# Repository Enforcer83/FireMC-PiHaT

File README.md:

# FireMC-3.14

FireMC for the Raspberry Pi HaT system

## 

This project has moved to https://gitlab.com/Enforcer83/FireMC-PiHaT.  See you there.

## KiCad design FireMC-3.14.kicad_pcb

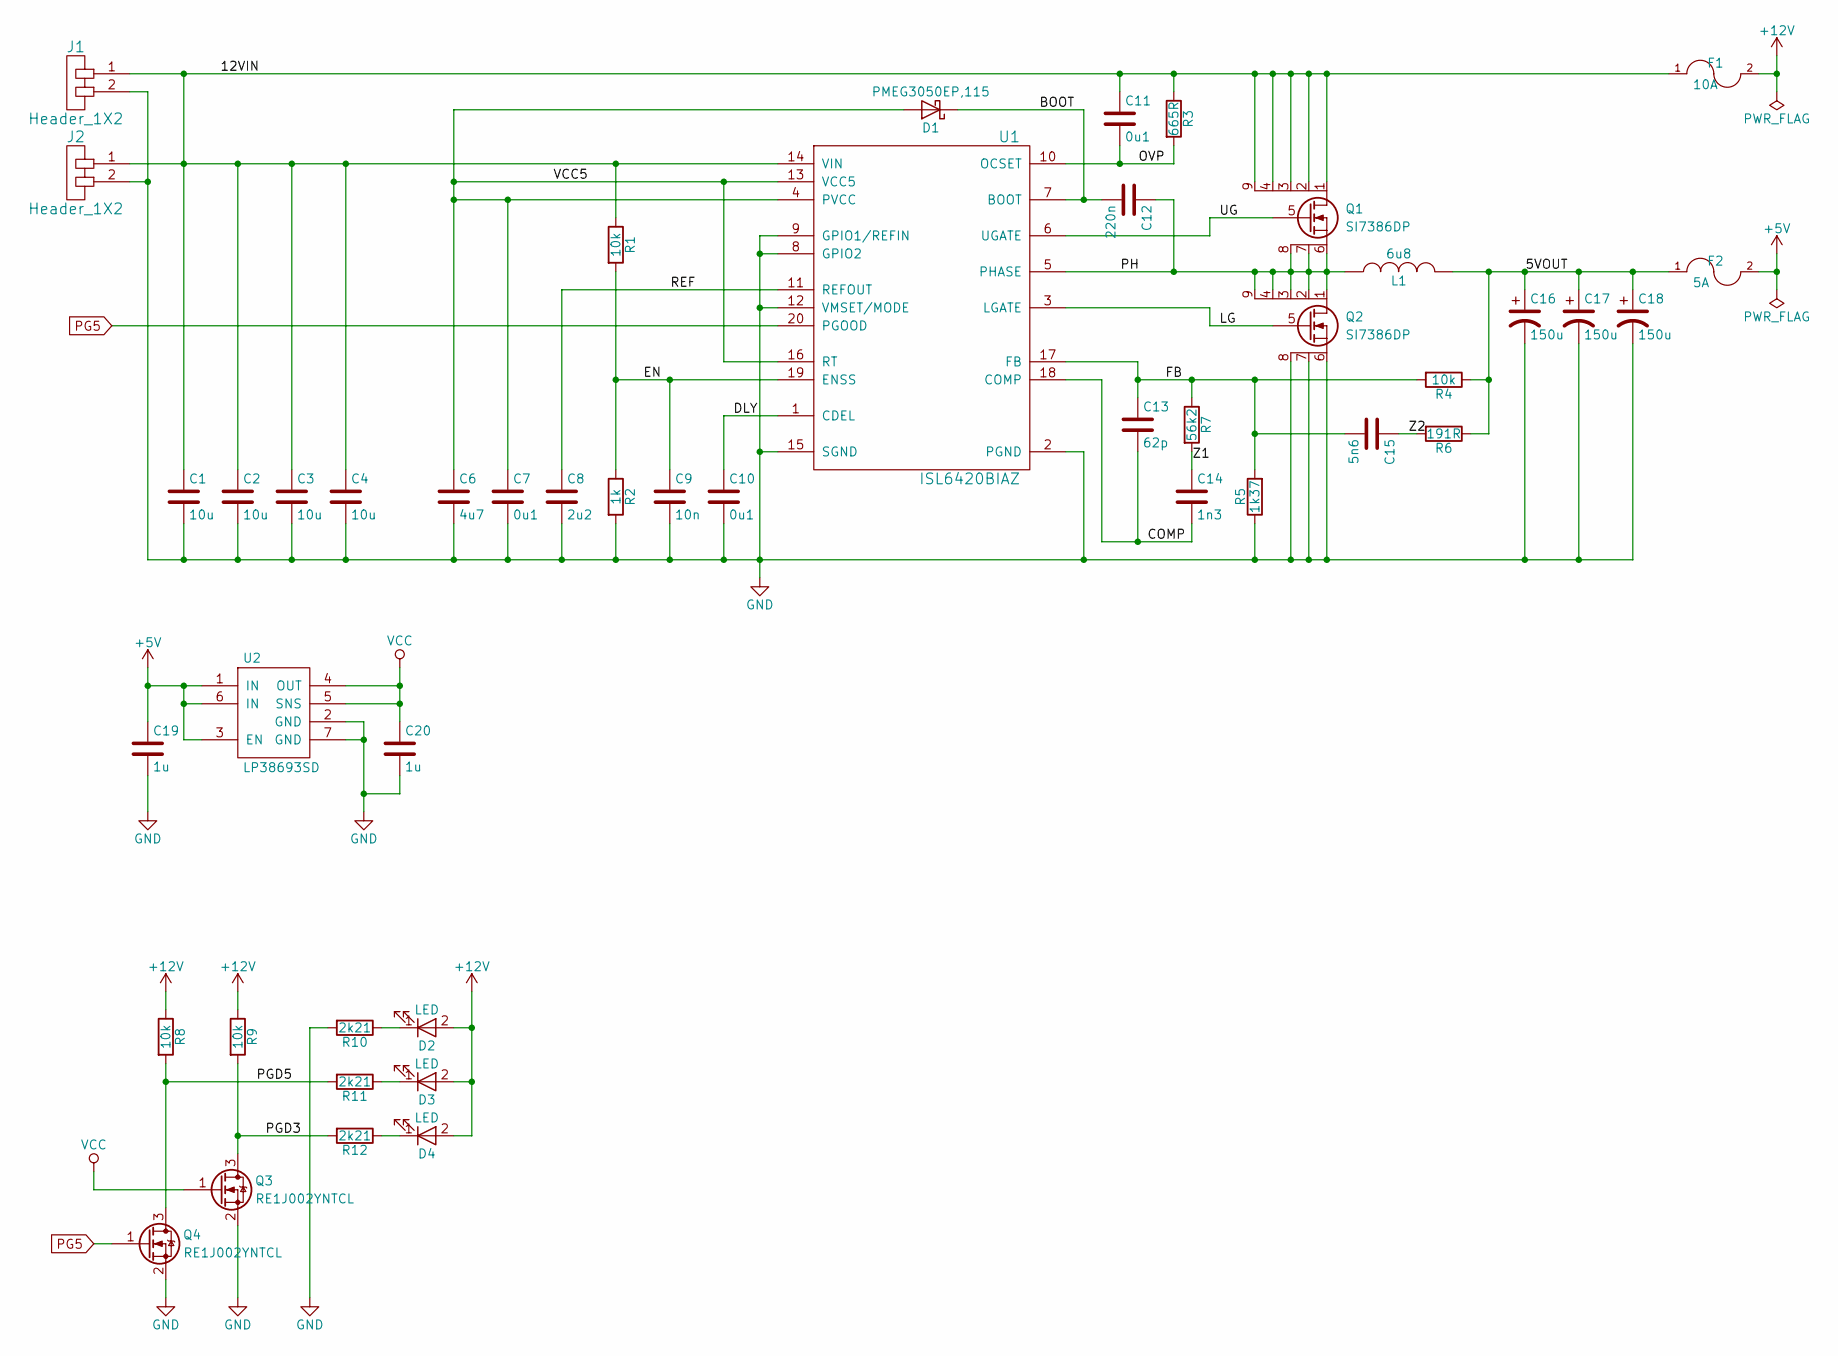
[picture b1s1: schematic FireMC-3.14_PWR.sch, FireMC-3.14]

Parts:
C1, C2, C3, C4: 10u; CAPC1608X95N
C6: 4u7; CAPC1608X95N
C7, C10, C11: 0u1; CAPC1608X90N
C8: 2u2; CAPC1608X90N
C9: 10n; CAPC1608X90N
C12: 220n; CAPC1608X90N
C13: 62p; CAPC1608X90N
C14: 1n3; CAPC1608X90N
C15: 5n6; CAPC1608X90N
C16, C17, C18: 150u; CAPAE660X770N
C19, C20: 1u; CAPC1608X90N
D1: PMEG3050EP,115; SOD4725X100N
D2, D3, D4: LED; LEDM1608X70N
F1: 10A; MPD_BK-6010; Mfg PN 0ATO010.V
F2: 5A; MPD_BK-6010; Mfg PN 0ATO005.V
J1: Header_1X2; MOLEX_395321002; MFG P/N 0395321002
J2: Header_1X2; PHEONIX_1923869; MFG P/N 1923869
L1: 6u8; INDM1213X620N
Q1, Q2: SI7386DP; SON9P127_490X590X112L61X41T376X348N
Q3, Q4: RE1J002YNTCL; SOTFL3P50_160X85L45X28N
R1, R4, R8, R9: 10k; RESC1608X55N
R2: 1k; RESC1608X55N
R3: 665R; RESC1608X55N
R5: 1k37; RESC1608X55N
R6: 191R; RESC1608X55N
R7: 56k2; RESC1608X55N
R10, R11, R12: 2k21; RESC1608X55N
U1: ISL6420BIAZ; SOP63P600X155-20N
U2: LP38693SD; SON7P95_300X300X80L40X35T210X160N

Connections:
+5V: C19.1, F2.2, U2.1 (IN), U2.3 (EN), U2.6 (IN); also elsewhere on the board
+12V: D2.2 (A), D3.2 (A), D4.2 (A), F1.2, R8.1, R9.1; also elsewhere on the board
/Power/5VOUT: C16.1, C17.1, C18.1, F2.1, L1.2, R4.1, R6.1
/Power/12VIN: C1.1, C2.1, C3.1, C4.1, C11.1, F1.1, J1.1, J2.1, Q1.1 (D), Q1.2 (D), Q1.3 (D), Q1.4 (D), Q1.9 (D), R1.1, R3.1, U1.14 (VIN)
/Power/BOOT: C12.2, D1.1 (K), U1.7 (BOOT)
/Power/COMP: C13.2, C14.2, U1.18 (COMP)
/Power/DLY: C10.1, U1.1 (CDEL)
/Power/EN: C9.1, R1.2, R2.1, U1.19 (ENSS)
/Power/FB: C13.1, C15.2, R4.2, R5.2, R7.1, U1.17 (FB)
/Power/LG: Q2.5 (G), U1.3 (LGATE)
/Power/OVP: C11.2, R3.2, U1.10 (OCSET)
/Power/PGD3: Q3.3 (D), R9.2, R12.2
/Power/PGD5: Q4.3 (D), R8.2, R11.2
/Power/PH: C12.1, L1.1, Q1.6 (S), Q1.7 (S), Q1.8 (S), Q2.1 (D), Q2.2 (D), Q2.3 (D), Q2.4 (D), Q2.9 (D), U1.5 (PHASE)
/Power/REF: C8.1, U1.11 (REFOUT)
/Power/UG: Q1.5 (G), U1.6 (UGATE)
/Power/VCC5: C6.1, C7.1, D1.2 (A), U1.4 (PVCC), U1.13 (VCC5), U1.16 (RT)
/Power/Z1: C14.1, R7.2
/Power/Z2: C15.1, R6.2
GND: C1.2, C2.2, C3.2, C4.2, C6.2, C7.2, C8.2, C9.2, C10.2, C16.2, C17.2, C18.2, C19.2, C20.2, J1.2, J2.2, Q2.6 (S), Q2.7 (S), Q2.8 (S), Q3.2 (S), Q4.2 (S), R2.2, R5.1, R10.2, U1.2 (PGND), U1.8 (GPIO2), U1.9 (GPIO1/REFIN), U1.12 (VMSET/MODE), U1.15 (SGND), U2.2 (GND), U2.7 (GND); also elsewhere on the board
unnamed: D2.1 (K), R10.1
unnamed: D3.1 (K), R11.1
unnamed: D4.1 (K), R12.1
PG5: Q4.1 (G), U1.20 (PGOOD)
VCC: C20.1, Q3.1 (G), U2.4 (OUT), U2.5 (SNS); also elsewhere on the board

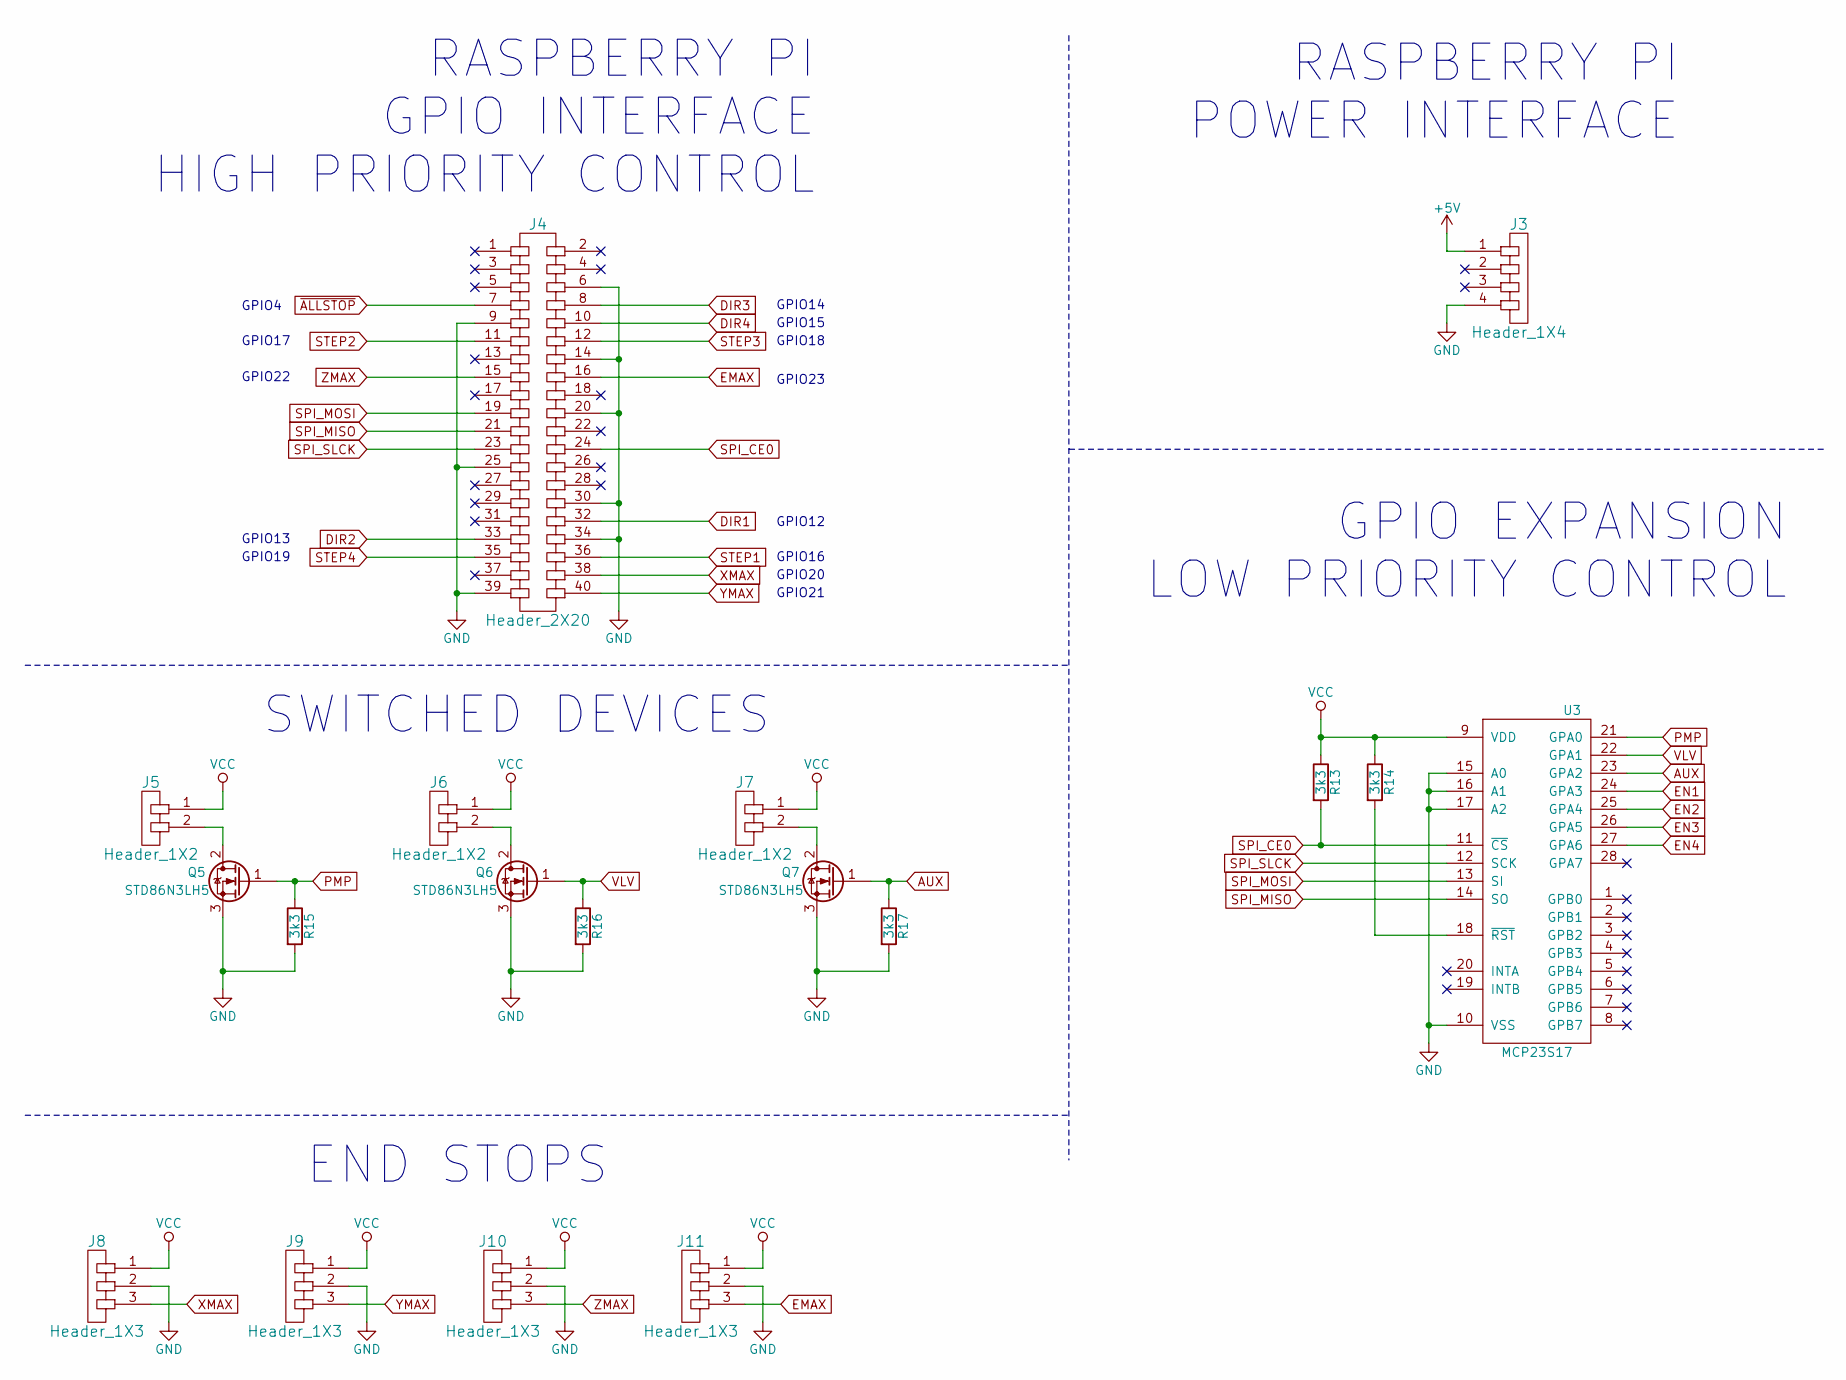
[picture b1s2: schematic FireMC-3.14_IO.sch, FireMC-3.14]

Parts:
J3: Header_1X4; MOLEX_22-23-2041
J4: Header_2X20; SULLINS_PPTC202LFBN-RC; Mfg PN PPPC200LFBN-RC
J5, J6, J7: Header_1X2; SULLINS_PRPC002SAAN-RC
J8, J9, J10, J11: Header_1X3; SULLINS_PRPC003SAAN-RC
Q5, Q6, Q7: STD86N3LH5; TO228P972X240-3N
R13, R14, R15, R16, R17: 3k3; RESC1608X55N
U3: MCP23S17; SOIC127P1030X265-28N

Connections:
+5V: J3.1; also elsewhere on the board
AUX: Q7.1 (G), R17.1, U3.23 (GPA2)
DIR1: J4.32; also elsewhere on the board
DIR2: J4.33; also elsewhere on the board
DIR3: J4.8; also elsewhere on the board
DIR4: J4.10; also elsewhere on the board
EMAX: J4.16, J11.3
EN1: U3.24 (GPA3); also elsewhere on the board
EN2: U3.25 (GPA4); also elsewhere on the board
EN3: U3.26 (GPA5); also elsewhere on the board
EN4: U3.27 (GPA6); also elsewhere on the board
GND: J3.4, J4.6, J4.9, J4.14, J4.20, J4.25, J4.30, J4.34, J4.39, J8.2, J9.2, J10.2, J11.2, Q5.3 (S), Q6.3 (S), Q7.3 (S), R15.2, R16.2, R17.2, U3.10 (VSS), U3.15 (A0), U3.16 (A1), U3.17 (A2); also elsewhere on the board
unnamed: J5.2, Q5.2 (D)
unnamed: J6.2, Q6.2 (D)
unnamed: J7.2, Q7.2 (D)
unnamed: R14.2, U3.18 (~RST)
PMP: Q5.1 (G), R15.1, U3.21 (GPA0)
SPI_CE0: J4.24, R13.2, U3.11 (~CS)
SPI_MISO: J4.21, U3.14 (SO)
SPI_MOSI: J4.19, U3.13 (SI)
SPI_SLCK: J4.23, U3.12 (SCK)
STEP1: J4.36; also elsewhere on the board
STEP2: J4.11; also elsewhere on the board
STEP3: J4.12; also elsewhere on the board
STEP4: J4.35; also elsewhere on the board
VCC: J5.1, J6.1, J7.1, J8.1, J9.1, J10.1, J11.1, R13.1, R14.1, U3.9 (VDD); also elsewhere on the board
VLV: Q6.1 (G), R16.1, U3.22 (GPA1)
XMAX: J4.38, J8.3
YMAX: J4.40, J9.3
ZMAX: J4.15, J10.3
~ALLSTOP: J4.7; also elsewhere on the board

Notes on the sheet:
RASPBERRY PI GPIO INTERFACE HIGH PRIORITY CONTROL
RASPBERRY PI POWER INTERFACE
GPIO EXPANSION LOW PRIORITY CONTROL
SWITCHED DEVICES
END STOPS
GPIO12
GPIO13
GPIO14
GPIO15
GPIO16
GPIO17
GPIO18
GPIO19
GPIO20
GPIO21
GPIO22
GPIO4
GPIO23

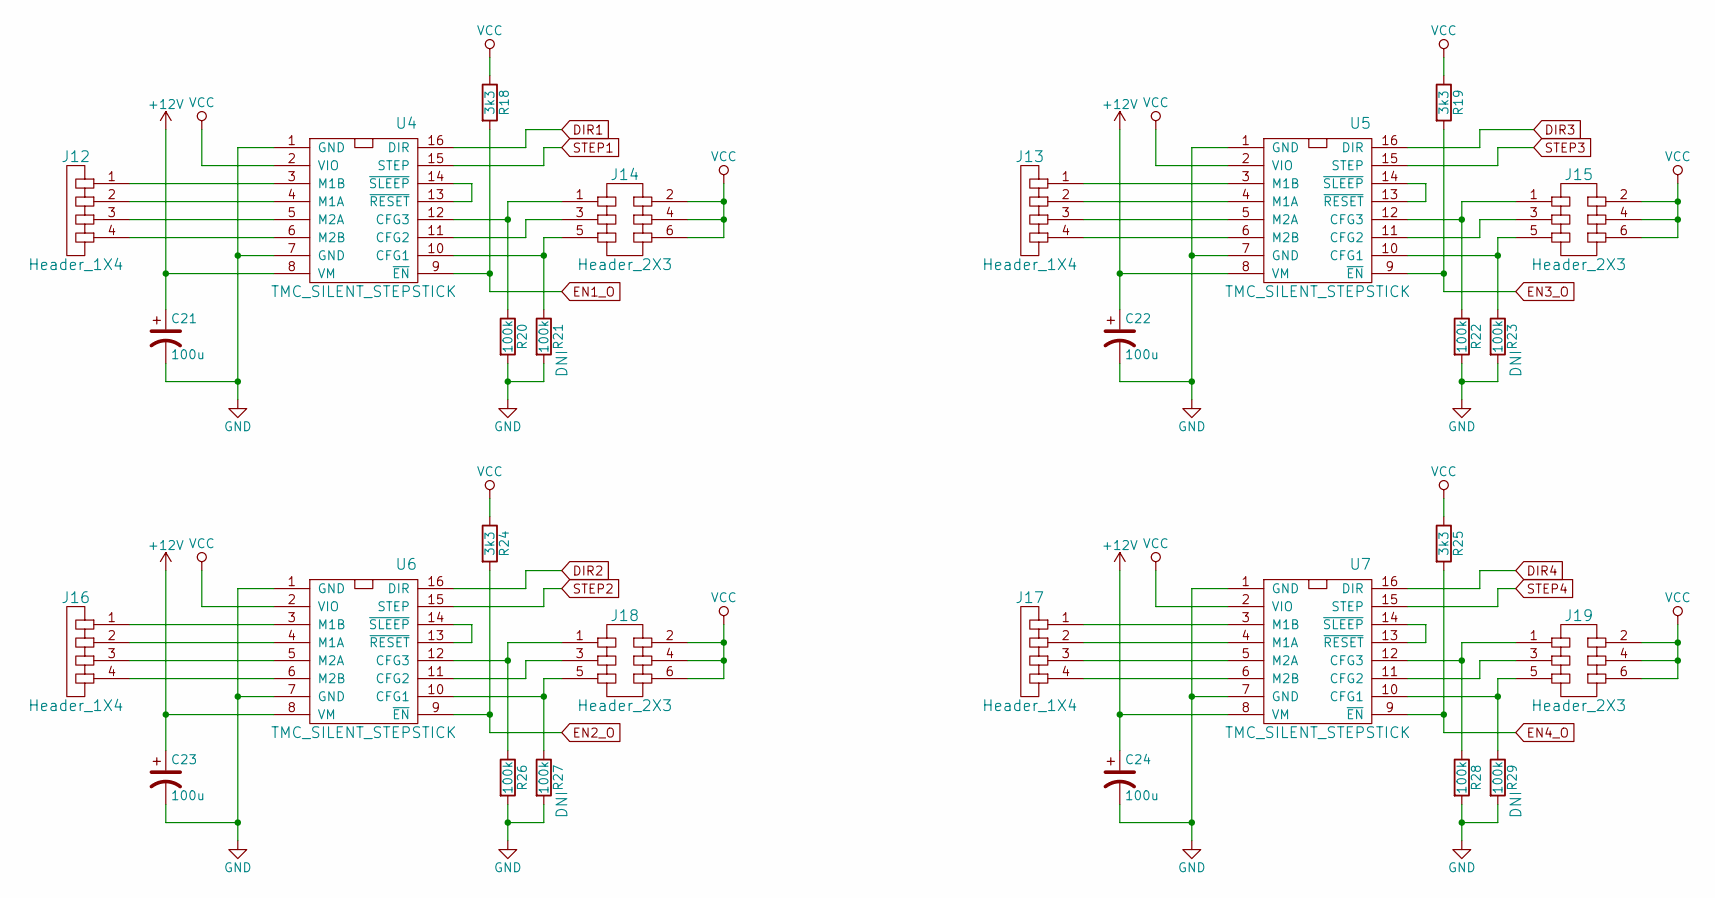
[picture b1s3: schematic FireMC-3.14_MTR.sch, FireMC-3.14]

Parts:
C21, C22, C23, C24: 100u; CAPAE840X650N
J12, J13, J16, J17: Header_1X4; SULLINS_PRPC004SAAN-RC
J14, J15, J18, J19: Header_2X3; TE_5-146254-3
R18, R19, R24, R25: 3k3; RESC1608X55N
R20, R21, R22, R23, R26, R27, R28, R29: 100k; RESC1608X55N
U4, U5, U6, U7: TMC_SILENT_STEPSTICK; stepstick

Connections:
+12V: C21.1, C22.1, C23.1, C24.1, U4.8 (VM), U5.8 (VM), U6.8 (VM), U7.8 (VM); also elsewhere on the board
DIR1: U4.16 (DIR); also elsewhere on the board
DIR2: U6.16 (DIR); also elsewhere on the board
DIR3: U5.16 (DIR); also elsewhere on the board
DIR4: U7.16 (DIR); also elsewhere on the board
EN1_O: R18.2, U4.9 (~EN); also elsewhere on the board
EN2_O: R24.2, U6.9 (~EN); also elsewhere on the board
EN3_O: R19.2, U5.9 (~EN); also elsewhere on the board
EN4_O: R25.2, U7.9 (~EN); also elsewhere on the board
GND: C21.2, C22.2, C23.2, C24.2, R20.2, R21.2, R22.2, R23.2, R26.2, R27.2, R28.2, R29.2, U4.1 (GND), U4.7 (GND), U5.1 (GND), U5.7 (GND), U6.1 (GND), U6.7 (GND), U7.1 (GND), U7.7 (GND); also elsewhere on the board
unnamed: J12.1, U4.3 (M1B)
unnamed: J12.2, U4.4 (M1A)
unnamed: J12.3, U4.5 (M2A)
unnamed: J12.4, U4.6 (M2B)
unnamed: J13.1, U5.3 (M1B)
unnamed: J13.2, U5.4 (M1A)
unnamed: J13.3, U5.5 (M2A)
unnamed: J13.4, U5.6 (M2B)
unnamed: J14.1, R20.1, U4.12 (CFG3)
unnamed: J14.3, U4.11 (CFG2)
unnamed: J14.5, R21.1, U4.10 (CFG1)
unnamed: J15.1, R22.1, U5.12 (CFG3)
unnamed: J15.3, U5.11 (CFG2)
unnamed: J15.5, R23.1, U5.10 (CFG1)
unnamed: J16.1, U6.3 (M1B)
unnamed: J16.2, U6.4 (M1A)
unnamed: J16.3, U6.5 (M2A)
unnamed: J16.4, U6.6 (M2B)
unnamed: J17.1, U7.3 (M1B)
unnamed: J17.2, U7.4 (M1A)
unnamed: J17.3, U7.5 (M2A)
unnamed: J17.4, U7.6 (M2B)
unnamed: J18.1, R26.1, U6.12 (CFG3)
unnamed: J18.3, U6.11 (CFG2)
unnamed: J18.5, R27.1, U6.10 (CFG1)
unnamed: J19.1, R28.1, U7.12 (CFG3)
unnamed: J19.3, U7.11 (CFG2)
unnamed: J19.5, R29.1, U7.10 (CFG1)
unnamed: U4.13 (~RESET), U4.14 (~SLEEP)
unnamed: U5.13 (~RESET), U5.14 (~SLEEP)
unnamed: U6.13 (~RESET), U6.14 (~SLEEP)
unnamed: U7.13 (~RESET), U7.14 (~SLEEP)
STEP1: U4.15 (STEP); also elsewhere on the board
STEP2: U6.15 (STEP); also elsewhere on the board
STEP3: U5.15 (STEP); also elsewhere on the board
STEP4: U7.15 (STEP); also elsewhere on the board
VCC: J14.2, J14.4, J14.6, J15.2, J15.4, J15.6, J18.2, J18.4, J18.6, J19.2, J19.4, J19.6, R18.1, R19.1, R24.1, R25.1, U4.2 (VIO), U5.2 (VIO), U6.2 (VIO), U7.2 (VIO); also elsewhere on the board

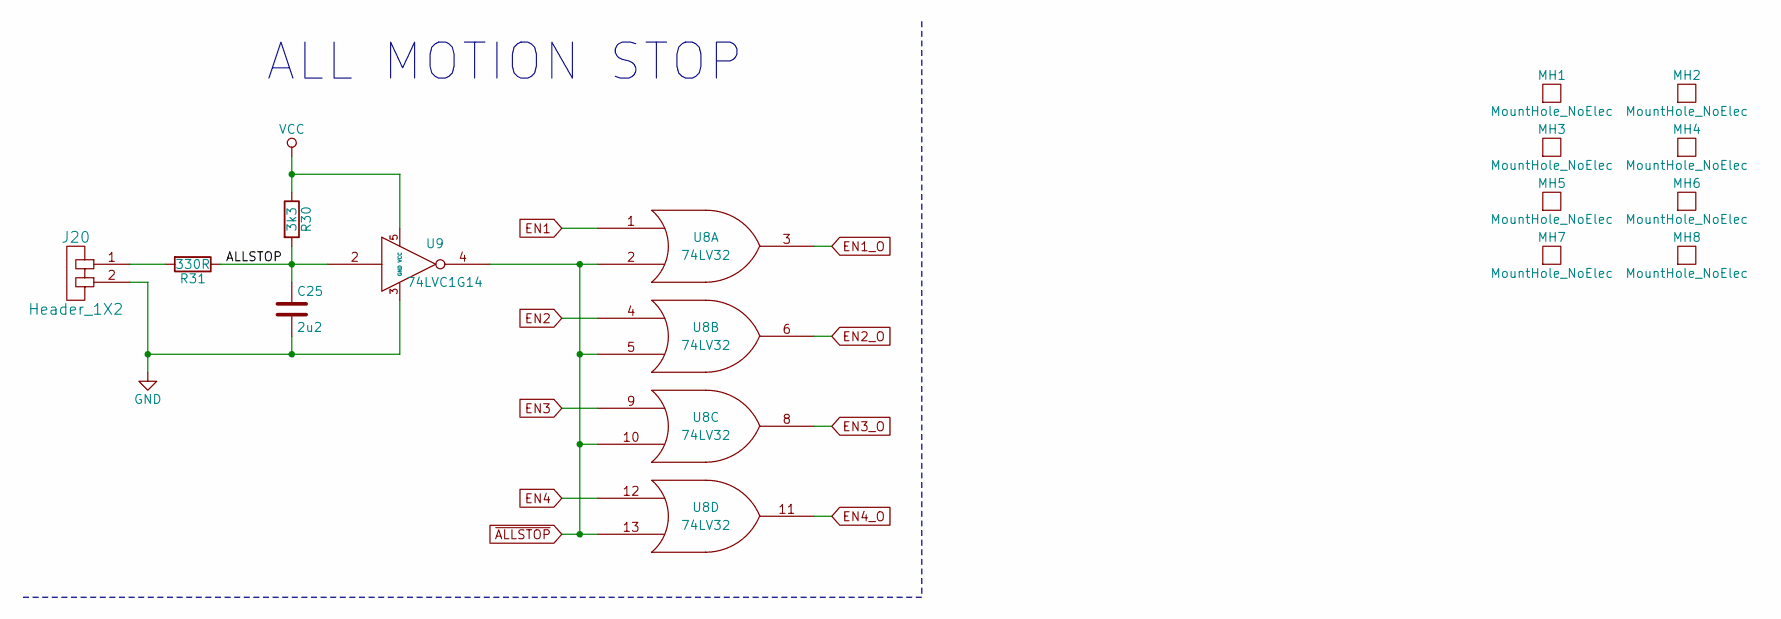
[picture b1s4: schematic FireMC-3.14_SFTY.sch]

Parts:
C25: 2u2; CAPC1608X90N
J20: Header_1X2; SULLINS_PRPC002SAAN-RC
MH1, MH2, MH3, MH4, MH5, MH6, MH7, MH8: MountHole_NoElec; IMELLC_MH275X600NPTH
R30: 3k3; RESC1608X55N
R31: 330R; RESC1608X55N
U8: 74LV32; SOP65P640X120-14N
U9: 74LVC1G14; SOT95P280X145-5N

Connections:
/Safety/ALLSTOP: C25.1, R30.2, R31.1, U9.2
EN1: U8.1; also elsewhere on the board
EN1_O: U8.3; also elsewhere on the board
EN2: U8.4; also elsewhere on the board
EN2_O: U8.6; also elsewhere on the board
EN3: U8.9; also elsewhere on the board
EN3_O: U8.8; also elsewhere on the board
EN4: U8.12; also elsewhere on the board
EN4_O: U8.11; also elsewhere on the board
GND: C25.2, J20.2, U8.7 (GND), U9.3 (GND); also elsewhere on the board
unnamed: J20.1, R31.2
VCC: R30.1, U8.14 (VCC), U9.5 (VCC); also elsewhere on the board
~ALLSTOP: U8.2, U8.5, U8.10, U8.13, U9.4; also elsewhere on the board

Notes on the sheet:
ALL MOTION STOP

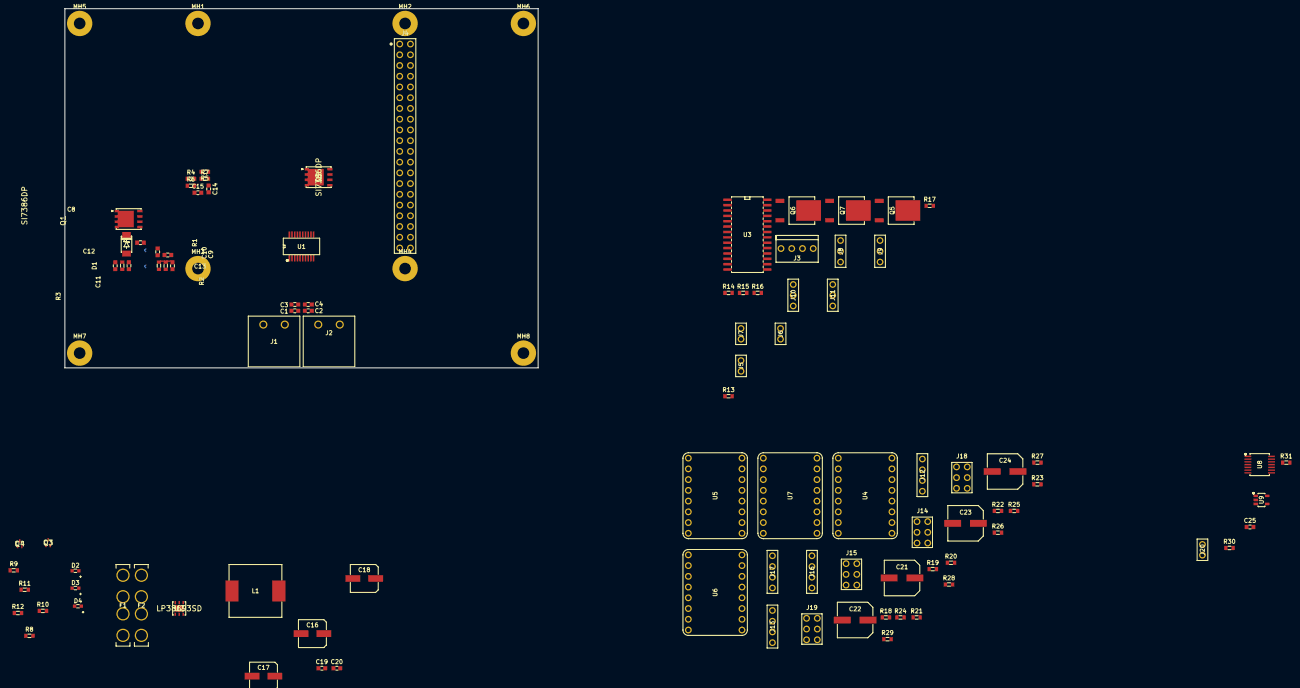
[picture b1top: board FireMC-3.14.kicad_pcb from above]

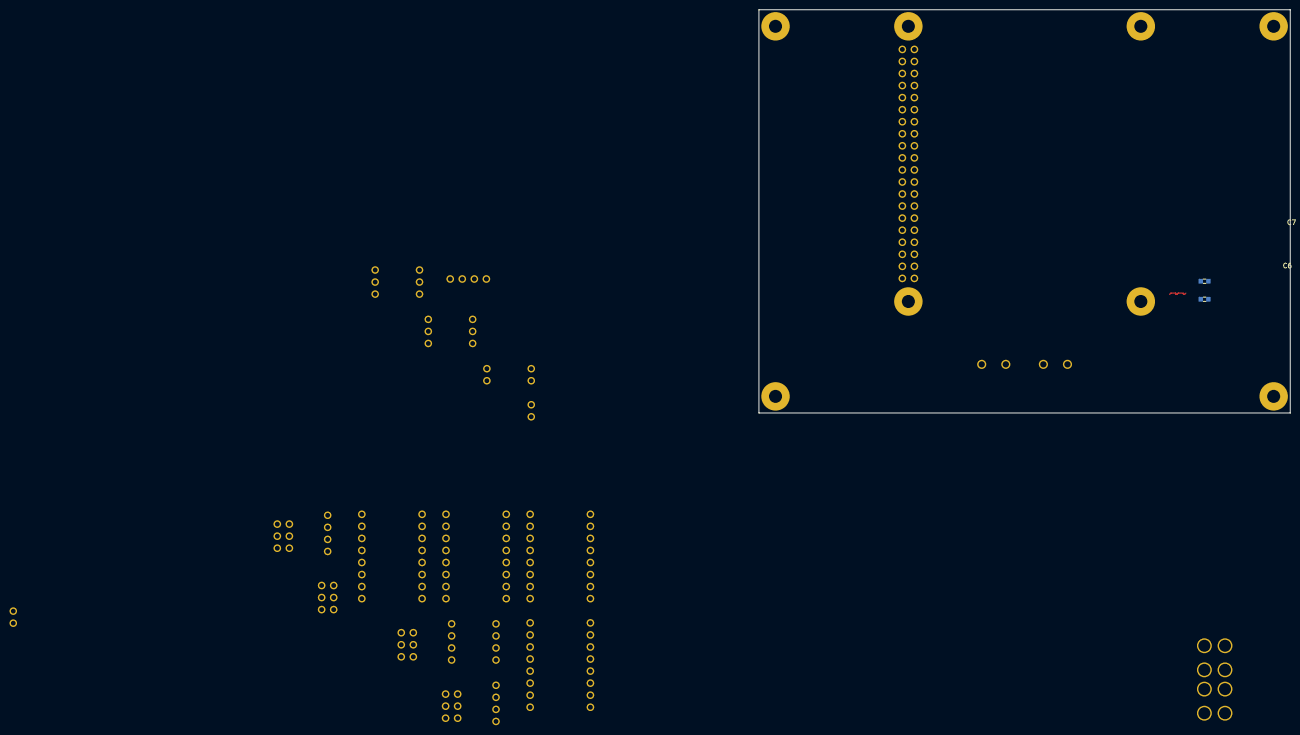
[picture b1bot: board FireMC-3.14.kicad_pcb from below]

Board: 2 copper layers, 112.0 x 85.0 mm, 106 parts (2 on the bottom side), 91 nets.

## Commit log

2016-08-12 Project Readme update
2016-08-12 defined purpose
2016-08-28 Week of 08/28/2016 update.
2016-08-31 Fully Populated Parts List With Currently selected parts
2016-09-04 Schematic work (Power, IO, Stepper)
2016-09-04 Created PDF of Schematic
2016-09-07 Schematic Update and Design Calcs for 3V3
2016-09-07 Typo correction
2016-09-07 Updated URL and Features
2016-09-08 Updated 8.2 uH Inductor PN and Desc
2016-09-08 Change MFG from Nippon to United Chemi-Con
2016-09-08 Added 10uF input capacitor
2016-09-08 corrected number of columns
2016-09-08 redo
2016-09-09 math check
2016-09-10 Schematic 80% complete
2016-09-11 added .gitignore file
2016-09-12 added schematic lib backup extension to gitignore
2016-09-12 Schematic corrections
2016-09-12 Schematic Complete for full comments
2016-09-12 True Complete with PDF
2016-09-20 Photo Interrupter Datasheet
2016-09-22 PCB Layout experimentation
2016-10-10 Time to Update. Board layout started.
2016-10-21 Board Layout Restart
2017-01-01 Update 1/1/2017
2017-02-14 Changed Power management
2017-02-26 KiCAD 4.0.5 Update corrections
2017-04-17 Pre-reformat Backup
2018-06-14 Project Moved
2018-06-14 Project Moved
    See the Readme.md file under the root directory
